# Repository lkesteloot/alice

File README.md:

# Alice website

Hardware projects from the 1990s and our revival and redesign starting in 2015 of that project and projects inspired by it. See the [web page](http://lkesteloot.github.io/alice/).

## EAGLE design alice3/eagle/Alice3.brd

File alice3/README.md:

# Alice III

This is the third model of the Alice machine. It runs a silicon Z80 with
two co-processors: an ARM for keyboard, disk, and serial port, and a Propeller for video.

The 80MHz Propeller has 48K of internal RAM, drives VGA and the 5-pin Aux connector (intended for audio but wired generically to 3 Propeller pins) and thus provides opportunities for video and other experimentation.

The 168MHz STM32F415 ARM Cortex-M4 contains 192K of RAM and is connected to a PS/2 port, an SD card, and a simple UART on a 2-pin header, and has a firmware monitor that can be altered or replaced.

In the `kicad` directory are various schematics and PCBs. The latest is
`MOBO_SMD`, which uses surface mount versions of the parts.

To bring up a new board:

* Power:
    * Use a wall wart to provide micro-USB power. Verify that the D2 LED
      (closest to the switches) is on.  If you have an in-line USB
      current meter, there should be less than 10 mA being initially pulled.
      (More is pulled later when the board is fully brought up.)
* Propeller:
    * Hook up the Prop Plug. The Vss pin should be closest to the corner of
      the board.
    * Run PropellerIDE, load the `video_board/propeller/Main.spin` file,
      and program the EEPROM. After this you should be able to hook up a VGA
      monitor and see the line `Alice 3 GPU firmware`.
    * Remove the Prop Plug.
* Cortex-M4:
    * Connect your computer to the USB jack of the Alice III.
    * Short the header closest to the ARM, labeled "JP1".
    * Hard-reset the board (the push button closest to the LEDs).
    * Wait one second, then remove the jumper.  If you look in your
      USB device list, you should see the STM bootloader.  For example,
      on MacOS X, the output of `system_profiler SPUSBDataType` should
      contain a section similar to:
```
        STM32  BOOTLOADER:

          Product ID: 0xdf11
          Vendor ID: 0x0483  (STMicroelectronics)
          Version: 22.00
          Serial Number: 366A34573335
          Speed: Up to 12 Mb/sec
          Manufacturer: STMicroelectronics
          Location ID: 0x14100000 / 20
          Current Available (mA): 1000
          Current Required (mA): 100
          Extra Operating Current (mA): 0
```
    * In `binaries`, run `sh install_cortex_m4_firmware.sh`.
        * `dfu-util` is a prerequisite.  It can be installed
	  on MacOS (our primary platform) through MacPorts, or you
	  can compile it from the source at
          `git://git.code.sf.net/p/dfu-util/dfu-util`.
    * To interact with the boot monitor:
        * Locate the 2-pin header closest to the MicroSD socket.
          There's no label on this header.
        * Attach a serial transceiver to this header; transmit to the pin
          closest to the ARM, and receive from the other pin.
          E.g. connect FTDI Tx to the pin closer to the ARM and
          FTDI Rx to the pin further from the ARM.
        * Connect to the serial port at 115200 baud.
        * When you hard-reset or power-on the Alice III, you should see
          on the serial port "Alice 3 I/O firmware" followed by the
          firmware build date.
* Z80:
    * Format a MicroSD card for FAT32.
    * Copy `binaries/bootrom.bin`, `binaries/boot.dsk` and `binaries/disks.txt` to the MicroSD card.
    * Install the MicroSD card in the Alice III and power-on or hard-reset the Alice III.

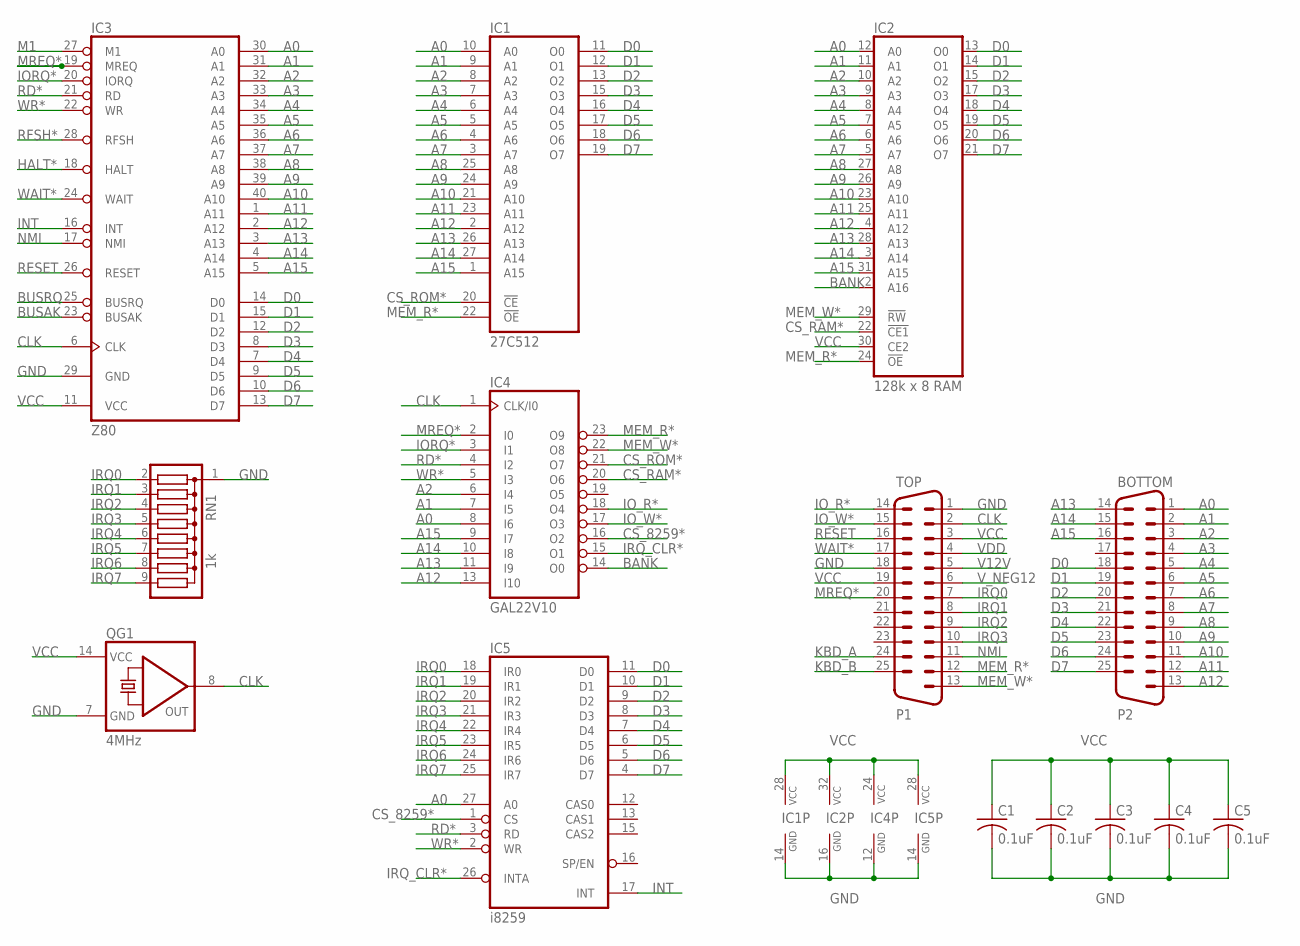
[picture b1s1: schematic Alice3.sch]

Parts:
BOTTOM: P2; M25HP
C1, C2, C3, C4, C5: 0.1uF; C1206
IC1: 27C512; DIL28
IC2: 128k x 8 RAM; DIL32
IC3: Z80; DIL40
IC4: GAL22V10; DIL24-3
IC5: i8259; DIL28-6
QG1: 4MHz; DIL14S
RN1: 1k; SIL9
TOP: P1; M25HP

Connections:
A0: BOTTOM.1, IC1.10 (A0), IC2.12 (A0), IC3.30 (A0), IC4.8 (I6), IC5.27 (A0)
A1: BOTTOM.2, IC1.9 (A1), IC2.11 (A1), IC3.31 (A1), IC4.7 (I5)
A2: BOTTOM.3, IC1.8 (A2), IC2.10 (A2), IC3.32 (A2), IC4.6 (I4)
A3: BOTTOM.4, IC1.7 (A3), IC2.9 (A3), IC3.33 (A3)
A4: BOTTOM.5, IC1.6 (A4), IC2.8 (A4), IC3.34 (A4)
A5: BOTTOM.6, IC1.5 (A5), IC2.7 (A5), IC3.35 (A5)
A6: BOTTOM.7, IC1.4 (A6), IC2.6 (A6), IC3.36 (A6)
A7: BOTTOM.8, IC1.3 (A7), IC2.5 (A7), IC3.37 (A7)
A8: BOTTOM.9, IC1.25 (A8), IC2.27 (A8), IC3.38 (A8)
A9: BOTTOM.10, IC1.24 (A9), IC2.26 (A9), IC3.39 (A9)
A10: BOTTOM.11, IC1.21 (A10), IC2.23 (A10), IC3.40 (A10)
A11: BOTTOM.12, IC1.23 (A11), IC2.25 (A11), IC3.1 (A11)
A12: BOTTOM.13, IC1.2 (A12), IC2.4 (A12), IC3.2 (A12), IC4.13 (I10)
A13: BOTTOM.14, IC1.26 (A13), IC2.28 (A13), IC3.3 (A13), IC4.11 (I9)
A14: BOTTOM.15, IC1.27 (A14), IC2.3 (A14), IC3.4 (A14), IC4.10 (I8)
A15: BOTTOM.16, IC1.1 (A15), IC2.31 (A15), IC3.5 (A15), IC4.9 (I7)
BANK: IC2.2 (A16), IC4.14 (O0)
BUSAK: IC3.23 (BUSAK)
BUSRQ: IC3.25 (BUSRQ)
CLK: IC3.6 (CLK), IC4.1 (CLK/I0), QG1.8 (OUT), TOP.2
CS_8259*: IC4.16 (O2), IC5.1 (CS)
CS_RAM*: IC2.22 (!CE1), IC4.20 (O6)
CS_ROM*: IC1.20 (!CE), IC4.21 (O7)
D0: BOTTOM.18, IC1.11 (O0), IC2.13 (O0), IC3.14 (D0), IC5.11 (D0)
D1: BOTTOM.19, IC1.12 (O1), IC2.14 (O1), IC3.15 (D1), IC5.10 (D1)
D2: BOTTOM.20, IC1.13 (O2), IC2.15 (O2), IC3.12 (D2), IC5.9 (D2)
D3: BOTTOM.21, IC1.15 (O3), IC2.17 (O3), IC3.8 (D3), IC5.8 (D3)
D4: BOTTOM.22, IC1.16 (O4), IC2.18 (O4), IC3.7 (D4), IC5.7 (D4)
D5: BOTTOM.23, IC1.17 (O5), IC2.19 (O5), IC3.9 (D5), IC5.6 (D5)
D6: BOTTOM.24, IC1.18 (O6), IC2.20 (O6), IC3.10 (D6), IC5.5 (D6)
D7: BOTTOM.25, IC1.19 (O7), IC2.21 (O7), IC3.13 (D7), IC5.4 (D7)
GND: C1.2, C2.2, C3.2, C4.2, C5.2, IC1.14 (GND), IC2.16 (GND), IC3.29 (GND), IC4.12 (GND), IC5.14 (GND), QG1.7 (GND), RN1.1, TOP.1, TOP.18
HALT*: IC3.18 (HALT)
INT: IC3.16 (INT), IC5.17 (INT)
IORQ*: IC3.20 (IORQ), IC4.3 (I1)
IO_R*: IC4.18 (O4), TOP.14
IO_W*: IC4.17 (O3), TOP.15
IRQ0: IC5.18 (IR0), RN1.2, TOP.7
IRQ1: IC5.19 (IR1), RN1.3, TOP.8
IRQ2: IC5.20 (IR2), RN1.4, TOP.9
IRQ3: IC5.21 (IR3), RN1.5, TOP.10
IRQ4: IC5.22 (IR4), RN1.6
IRQ5: IC5.23 (IR5), RN1.7
IRQ6: IC5.24 (IR6), RN1.8
IRQ7: IC5.25 (IR7), RN1.9
IRQ_CLR*: IC4.15 (O1), IC5.26 (INTA)
KBD_A: TOP.24
KBD_B: TOP.25
M1: IC3.27 (M1)
MEM_R*: IC1.22 (!OE), IC2.24 (!OE), IC4.23 (O9), TOP.12
MEM_W*: IC2.29 (!RW), IC4.22 (O8), TOP.13
MREQ*: IC3.19 (MREQ), IC4.2 (I0), TOP.20
NMI: IC3.17 (NMI), TOP.11
RD*: IC3.21 (RD), IC4.4 (I2), IC5.3 (RD)
RESET: IC3.26 (RESET), TOP.16
RFSH*: IC3.28 (RFSH)
V12V: TOP.5
VCC: C1.1, C2.1, C3.1, C4.1, C5.1, IC1.28 (VCC), IC2.30 (CE2), IC2.32 (VCC), IC3.11 (VCC), IC4.24 (VCC), IC5.28 (VCC), QG1.14 (VCC), TOP.3, TOP.19
VDD: TOP.4
V_NEG12: TOP.6
WAIT*: IC3.24 (WAIT), TOP.17
WR*: IC3.22 (WR), IC4.5 (I3), IC5.2 (WR)

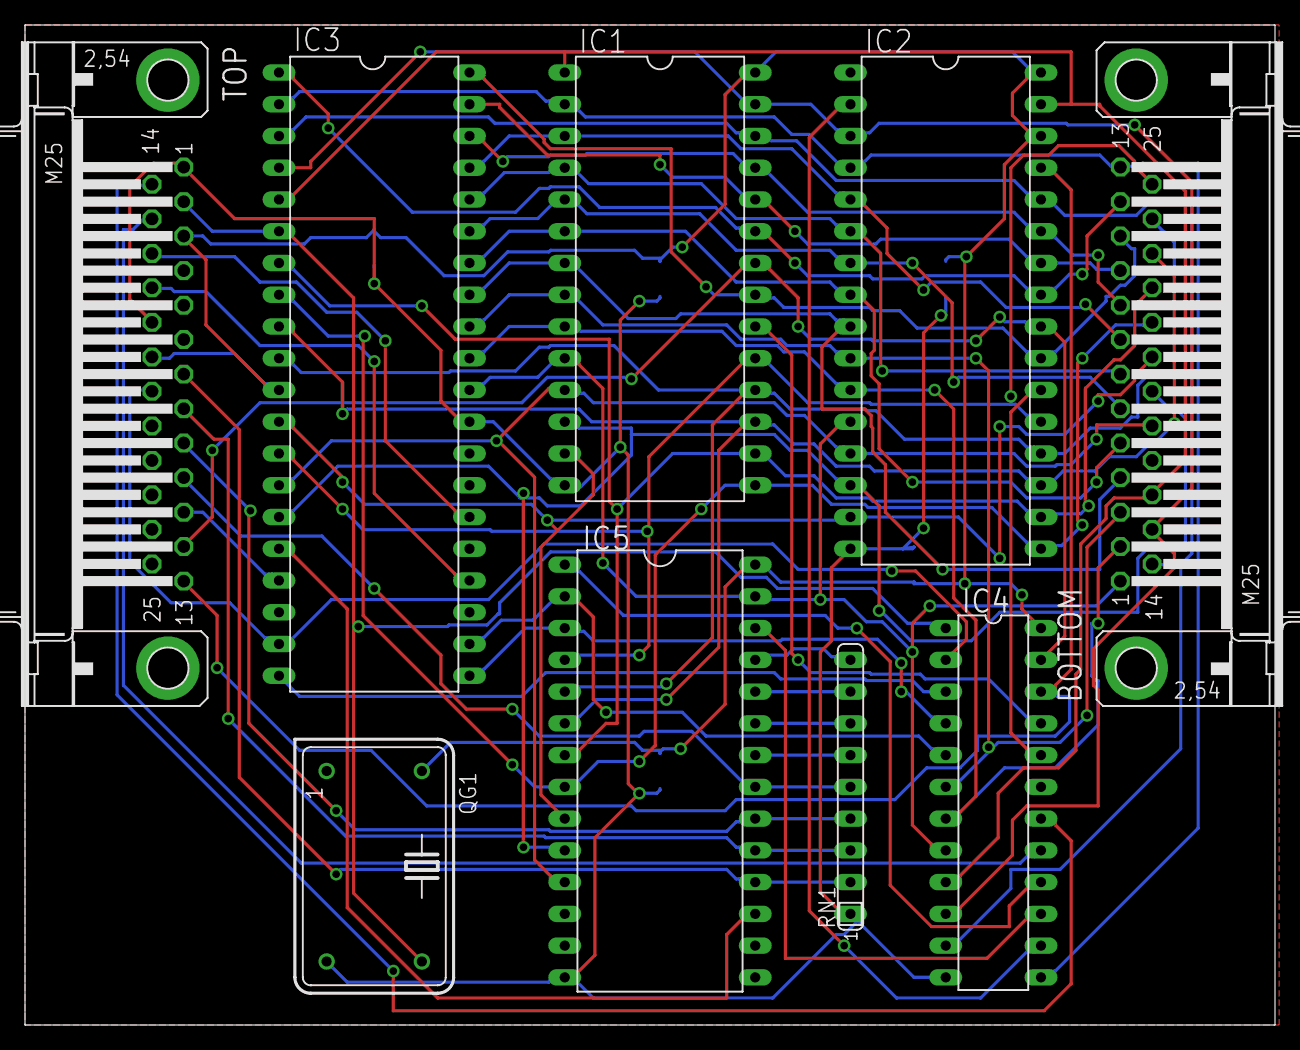
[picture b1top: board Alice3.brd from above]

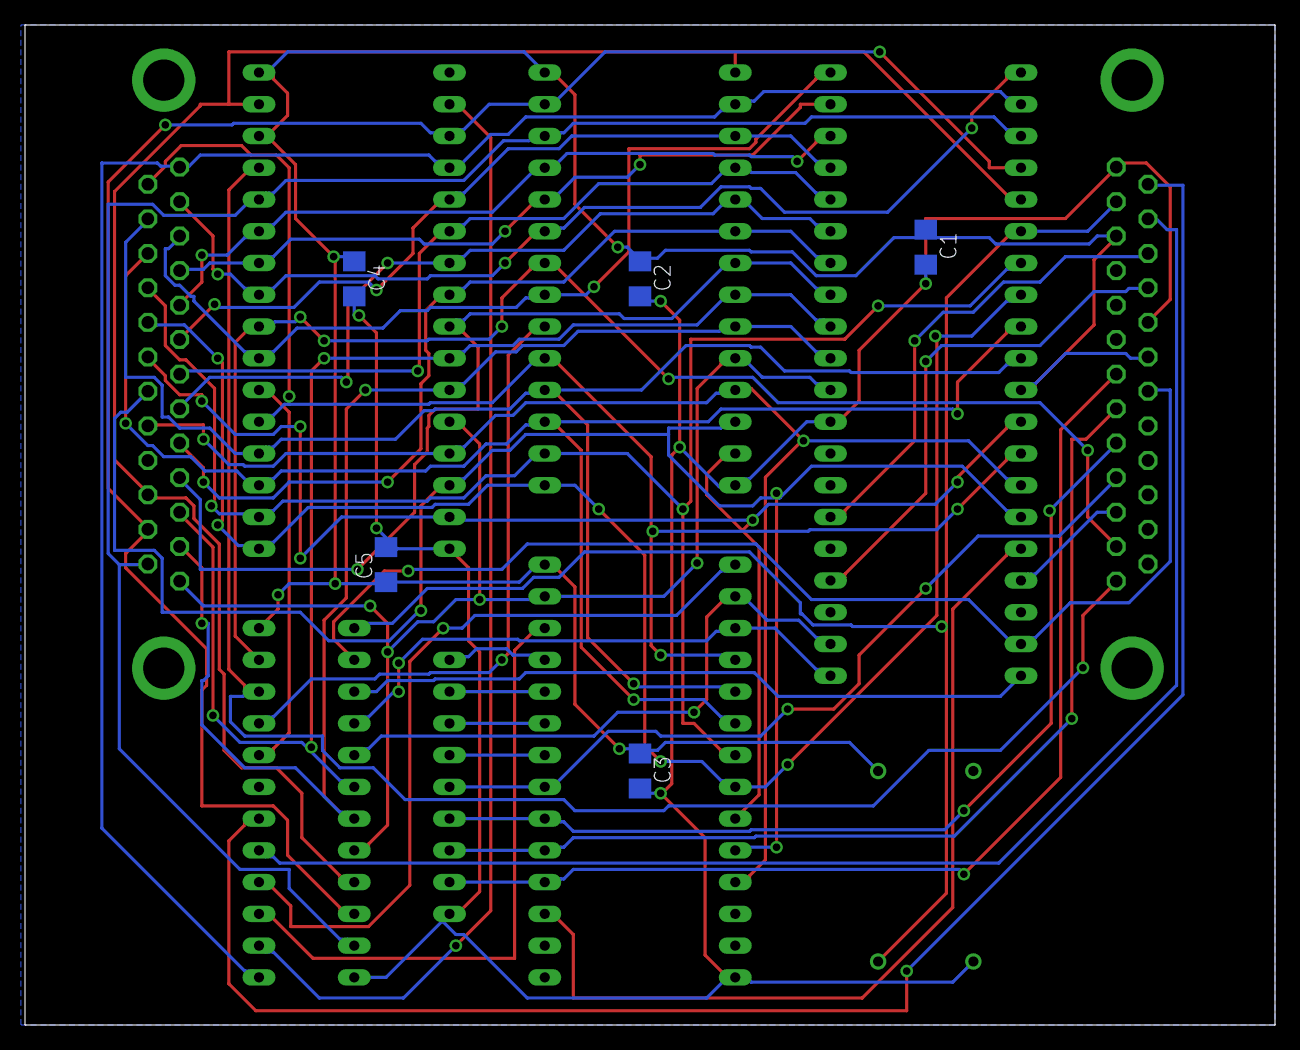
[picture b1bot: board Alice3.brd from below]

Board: 2 copper layers, 100.0 x 80.0 mm, 14 parts (5 on the bottom side), 52 nets.

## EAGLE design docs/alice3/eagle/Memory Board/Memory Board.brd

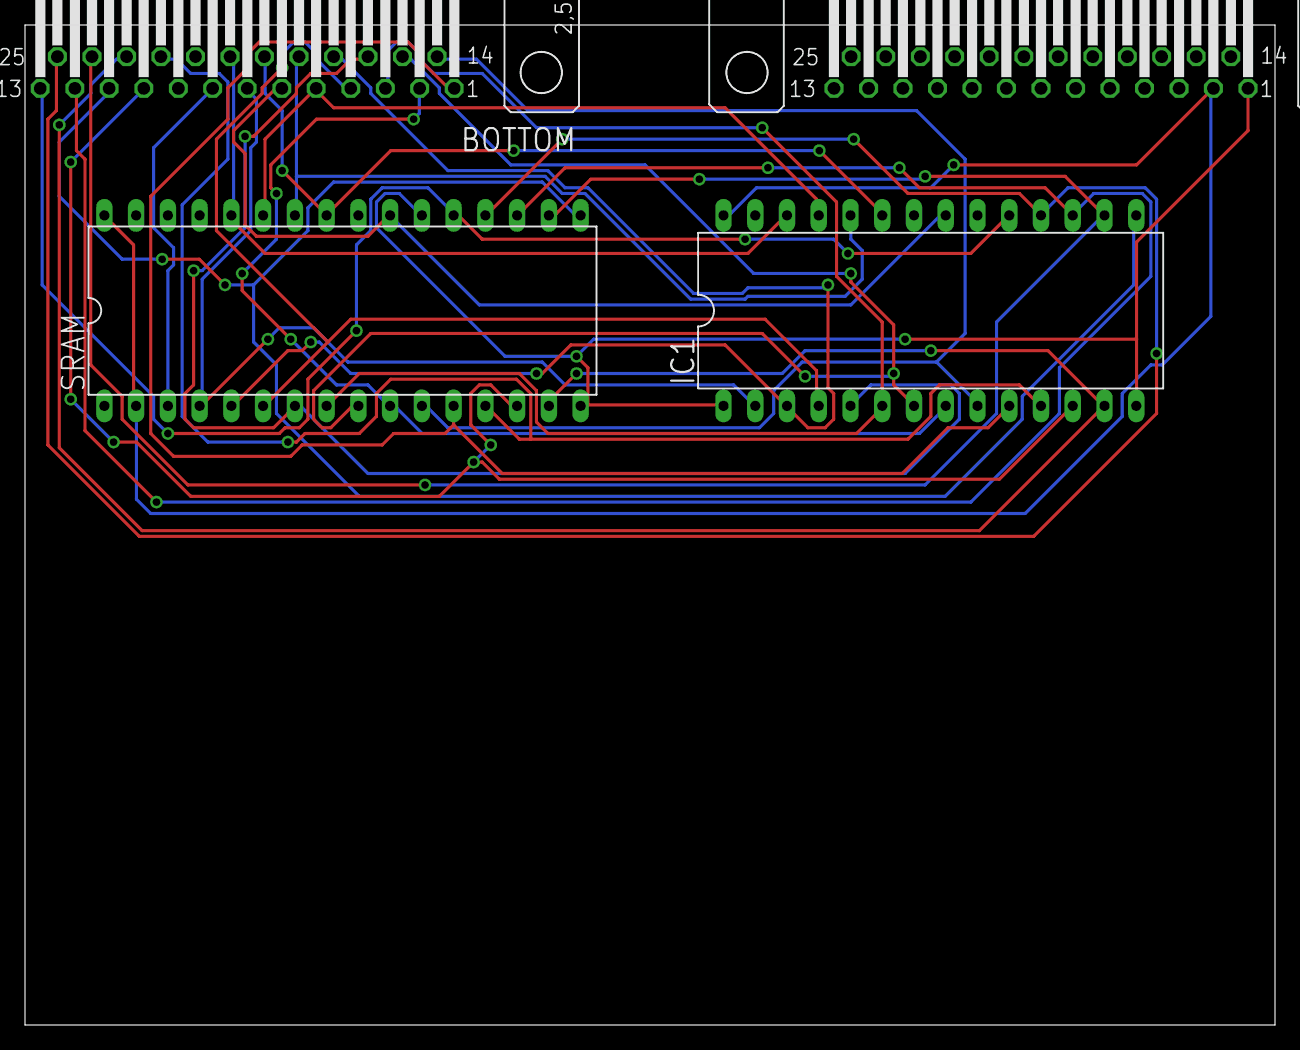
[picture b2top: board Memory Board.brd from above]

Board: 2 copper layers, 100.0 x 80.0 mm, 4 parts (0 on the bottom side), 25 nets.

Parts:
BOTTOM: M25H
IC1: 27C128P; DIL28-6
SRAM: DIL32
TOP: M25H

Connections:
+5: IC1.28, SRAM.2, SRAM.32, TOP.2
A0: BOTTOM.1, IC1.10, SRAM.12
A1: BOTTOM.14, IC1.9, SRAM.11
A2: BOTTOM.2, IC1.8, SRAM.10
A3: BOTTOM.15, IC1.7, SRAM.9
A4: BOTTOM.3, IC1.6, SRAM.8
A5: BOTTOM.16, IC1.5, SRAM.7
A6: BOTTOM.4, IC1.4, SRAM.6
A7: BOTTOM.17, IC1.3, SRAM.5
A8: BOTTOM.5, IC1.25, SRAM.27
A9: BOTTOM.18, IC1.24, SRAM.26
A10: BOTTOM.6, IC1.21, SRAM.23
A11: BOTTOM.19, IC1.23, SRAM.25
A12: BOTTOM.7, IC1.2, SRAM.4
A13: BOTTOM.20, IC1.26, SRAM.28
A14: BOTTOM.8, SRAM.3
D0: BOTTOM.22, IC1.11, SRAM.13
D1: BOTTOM.10, IC1.12, SRAM.14
D2: BOTTOM.23, IC1.13, SRAM.15
D3: BOTTOM.11, IC1.15, SRAM.17
D4: BOTTOM.24, IC1.16, SRAM.18
D5: BOTTOM.12, IC1.17, SRAM.19
D6: BOTTOM.25, IC1.18, SRAM.20
D7: BOTTOM.13, IC1.19, SRAM.21
GND: IC1.1, IC1.14, SRAM.16, SRAM.22, TOP.1

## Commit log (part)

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2017-04-15 Fix various bugs in FIFO code.
2017-04-15 Can increment in memtool.
2017-04-15 Convert image to 32bits before accessing
2017-04-16 Pretty stable frame buffer.
2017-04-16 Double size of FIFO to avoid underrun.
2017-04-16 Encapsulate touchscreen in its own unit
2017-04-16 Add beginnings of events on hardware
2017-04-16 Add ERROR prints on unexpected conditions
2017-04-17 Move flush so gl.c is not dependent on network
2017-04-17 Add platform.mk file for choosing implementation
    Edit platform.mk to change the implementaiton of the rasterizer and events.
2017-04-17 More careful LCD pixel output.
2017-04-19 Convert output to G's
2017-04-24 Add second memory interface.
2017-04-24 Modify memtool to support 64-bit writes and reads.
2017-04-24 Protocol test program.
2017-04-24 Draw bounding box of triangle.
2017-04-24 Turn of debug printf and usleep() now that we block on swap buffers.
2017-04-25 Respect triangle color; display count of unhandled commands.
2017-04-25 Make GPU command buffer - not tested
2017-04-26 Correct check for mmap() failure (not compiled or tested).
2017-04-26 Change DEBUG_PRINT to undef
2017-04-27 Reset buffer after each frame.
2017-04-27 Put image in both framebuffers
    Make new put_image function.
    Put the fipImage in both framebuffers that may be scanned out.
    Center image correctly in dimensions less than the framebuffer size.
2017-04-27 Add a utility to save the framebuffers as images
    Save off each framebuffer using FreeImagePlus.
    FIP will automatically use an encoder matching the filename extension entered.
    e.g. sudo alice4save framebuffer0.png framebuffer1.jpg # not that you'd do this, but it works
    Hardcode the framebuffer location, rowbytes, and bpp for convenience.
2017-04-28 Spin triangle more slowly in the test.
2017-04-28 Disable networking in Arena, it doesn't compile on the embedded Linux.
2017-04-29 Bigger FB FIFO and latch the debug text.
2017-04-30 Compare open against -1 to detect failure
    OMG, this is kind of embarrassing.
2017-04-30 Fix tied evaluator record and read
    Fix cut-and-paste error in tied evaluator loop - set loop variable k but did not use it to read evaluator device
    Fix events_tie() - was not using the correct array index
2017-05-01 Software side of pattern.
2017-05-01 Add code to parse PATTERN (untested)
2017-05-01 Implement patterns in FPGA.
2017-05-02 Add pattern test to protocol program.
2017-05-02 Add optimization to all Makefiles
    This change boosts logo's CPU-only frame rate from 25 frames per second to 95.
2017-05-03 Double-buffer the command stream
    If "double_buffer_commands" is set to 0, commands are written directly to the GPU memory buffer for commands. (Therefore no additional commands can be safely written to the buffer until the GPU has f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
    If "double_buffer_commands" is set to 1, commands are written directly to a separate "staging" memory buffer. "swap" waits until any previous GPU work is complete, meaning the GPU buffer can be writt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
    N.B. By default now set double_buffer_commands to 1. It is a const variable me
2017-05-03 Expose front buffer bit.
2017-05-04 Add frame stats per-frame and averaged over a second
    PRINT_FRAME_STATS=1 will print ms for some portions of the frame every second.
    PRINT_FRAME_STATS=2 will print ms for some portions of the frame every frame.
2017-05-04 Program to pulse LCD backlight.
2017-05-04 Fix bounding box calculation.
2017-05-04 Modify fpgasim to do more efficient color interpolation.
2017-05-04 Print time spent waiting on raster finish
2017-05-04 Revert accidental change to platform makefile.
2017-05-04 Write overlay in single-bit red so as to not disturb the LCD. Need to investigate why this is necessary.
2017-05-05 add -lm for Linux build
2017-05-08 Tilt test over VNC
    Prints "TILT_VALID" and tilt valuators when tilt is within accurate ranges.
    Prints "TILT_INVALID" and does not print valuators when tilt is out of range.
2017-05-13 Add two stages to the reciprocal (from 4 to 6) to eliminate timing warnings.
    Fixes #34.
2017-05-17 Add modes for just ramp and for delaying all bits
    Change size to 800x480 so that output matches Alice 4 display
    - notably the ramp can be loaded into Alice 4 display to illustrate issues
    "make" creates all three images.
    Provide "--all8bits" to delay all 8 bits of the color, showing close to what Brad sees.
    Provide "--justramp" to output the color ramp with no output effect.
2017-05-18 Add Z buffer test to protocol.cpp.
2017-05-22 DISPLAY_ENABLE -> DATA_ENABLE
2017-05-22 Add some boards and chips we're using
    Adafruit Bluefruit LE SPI
    Adafruit L3GD20H breakout
    Adafruit PowerBoost 1000c
    STM STMPE811
2017-05-22 Add memory controller ports for Z.
2017-05-24 Add write FIFO and use it for color.
2017-05-24 Interpolate Z.
2017-05-24 Move i2c functions into utility module
2017-05-24 Accelerometer module
2017-05-24 Fix math error converting radians to degres
2017-05-24 Smooth accelerometer with exponential decay
    Add (current sensor reading * (1 - decay)) to (old * decay).
    Smoothing helps somewhat with decay = .5. Decay = .8 looks a lot better but loses rapid motion.
    Committing decay = 0.5.
2017-05-25 Clean up Verilog code.
2017-05-26 Fix Z buffer artifacts. Fixes #13.
2017-05-26 Add stats to protocol test.
2017-05-26 Clear Z in protocol test.
2017-05-28 Remove test code.
2017-05-28 Add notes for test fifo.
2017-05-29 Speed up rasterization. Fixes #40.
2017-05-29 Fix use of fifo.empty in read fifo.
2017-06-02 Always spin object slowly, fix Z
    Remove call to gversion and machine-dependent Z setup.
    Use default Z function, back-to-front values for lsetdepth, and clear Z to far.
    Set "spin" to default to TRUE and spin 1/3 as fast as it was spinning.
2017-06-03 Add tilt
2017-06-04 Rasterize lines
2017-06-04 Rasterize lines more correctly
    Draw boxes that represent lines by extending line by linewidth along
    axis perpendicular to the line's major axis, resulting in parallelograms.
2017-06-04 Factor out libawesome.
2017-06-04 Add home support to protocol test program.
2017-06-04 Use one global Awesome
    Move struct definition into awesome.c.
    Keep one global Awesome instance in awesome.c.
    Remove all Awesome pointers from awesome functions.
    Fixup protocol test to match.
2017-06-04 Don't pass a pointer to an Awesome
2017-06-04 Warn if we skip a frame.
2017-06-04 Add Arena
2017-06-04 compile with networking
2017-06-04 Implement czclear(), fix #39
    Implement czclear in rasterizer interface and rasterizer implementations.
    In hardware_rasterizer, pass czclear to libawesome
    Use czclear in logo and jello (already used in bounce)
2017-06-04 Set ESC (Home) to exit only submenus in buttonfly
2017-06-04 Add ability to dump logo commands to a file. For #22.
2017-06-04 Add Make target for writing logo.bin to SD card.
2017-06-05 Add memory thrashing tool.
2017-06-11 Fix line endings for u-boot.txt.
2017-06-12 Re-enable double buffering of commands.
2017-06-12 Break up long thin triangles. For issue #17.
    Long thin (diagonal) triangles waste a lot of time in the
    rasterizer because we consider every point in the bounding
    box. With this change, if the ratio of triangle pixels
    to bounding box pixels is low, we tesselate the triangle.
    This halves the number of bounding box pixels (1.8m to 0.9m)
    at the slowest frame of buttonfly. (The bevel of the button
2017-06-12 Configure extra memory ports.
2017-06-16 add network events example in a comment
2017-06-16 fix array overrun
2017-06-16 Avoid divide by zero when displaying statistics.
2017-06-16 Don't start reading command buffer until we're ready.
2017-06-16 Bogus no-op changes by Quartus.
2017-07-15 Update overview page.
2017-07-15 Fix up Alice 2 docs.
2017-07-15 Load fonts over https.
2017-07-15 Use arabic numerals instead of roman ones for Alice version numbers.
2017-07-15 Add stub Alice 4 page.
2017-07-20 Disable blinking LED.
2017-07-26 Don't show arena instructions. Fixes #58.
2017-07-26 Add disabled code to split up lines.
2017-08-02 Add Makefile targets to start/stop service.
2017-08-03 IrisGL transformation and lighting benchmark
2017-08-04 Don't enable shutdown in Makefile.
2017-08-04 Dummy events in platform Makefile.
2017-08-05 Fix aspect ratio of ideas.
2017-08-05 Replace shutdown with ideas.
2017-08-06 Final flight changes to make it build.
2017-08-06 Fix flight warnings and clear bug in gl.
2017-08-08 Run the 747 by default in flight.
2017-08-09 Link to web page.
2017-08-09 Add secret menu.
2017-08-10 switch interaction to that of jello
2017-08-10 render all 6 walls with faceculling
2017-08-15 Big VCF West 2017 commit
    Terminal.spin: complete rewrite in prop asm, lots more codes handled,
    jump table used which should provide a good example for streamlining in
    the future
    Bus_interface.spin: better documentation at the top, added serial terminal
    mirroring but commented-out, added ay_allatonce handler, added ay_BEL
    Main.spin: added another row to the buffer for easier terminal scrolling
2017-08-15 Added JDCogSerial.spin to alice3/video_board/propeller directory since the alternative commented-out terminal code in Main.spin references it
2017-08-16 make CE2 high
2017-08-16 draft DABO2 PCB
2017-08-16 footprints
2017-08-17 increase SD speed to about 21MHz after init
2017-08-17 ARM fimware binary with faster SD access
2017-08-19 catch correct enum for WRITE_DMA
2017-08-19 implement ARM firmware for DMA READ and WRITE
2017-08-26 set up RFSH and WAIT signals correctly
2017-08-28 1st set MOBO schematic fixes for 1st PCBWay spin
    Various fixes for KiCAD messing up components
    Button on BOOT0
    No huge cap on power supply LED
    Discard RAM
    Route ARM to Z80 /WAIT and /RFSH
    Use "~" for active-low lines (shown in schematic by line above them)
2017-08-29 V4 improvements round 2
    Label buttons, LEDs, and connectors
    Delete footprints for deleted schematic parts
    Move microUSB jack and space out PS2, VGA connectors
    Position SMT Propeller crystal
    Change BOOT0 header to button
    Delete RAM
2017-08-29 consolidate all Z80 addr pins on one ARM port
2017-09-06 fix misspelling of "staging"
2017-09-07 constant current part FAN5333A/B
2017-09-07 integrate constant current driver, drop TFT Friend
2017-09-08 replace L3DG20H breakout with actual chip
2017-09-09 TPS61090 boost supply
2017-09-10 add source files for components
2017-09-11 run LIPO to STMPE811 ADC on IN0
2017-09-13 Add link to red button.
2017-09-13 Acrylic enclosure.
2017-09-13 l3gd20h qfn footprint
2017-09-13 first draft of layout
2017-09-14 add hidden PAD pins that are GND
2017-09-14 Second draft of layout
    Lawrence fixes to schematic
    Layout PCB
2017-09-16 remove R pulling PWREN to VBAT
2017-09-17 one more draft layout; better 3v3 plane
2017-09-18 add SMD 1206 testpoint pad footprint
2017-09-18 Hopefully near final layout
2017-09-27 Add jac library including large hole
2017-09-29 add ideas
2017-09-29 rotate 180 degrees
2017-10-10 Fix up WaveDrom for write FIFO.
2017-10-12 Minor tweaks to write-up.
2017-10-16 Better motivation for area reciprocal.
2017-10-16 Get flight to compile on Alice 4.
2017-10-16 Slower accelerator decay.
2017-10-16 Fix secret menu.
2017-10-16 Re-enable culling, implement correctly
    Ideas now works and the bounce models (except for doughnut?!) work properly and at full rate
2017-10-22 Start Verilator simulation integration.
2017-10-22 Add Frame buffer to Verilator.
2017-10-24 Add and link placeholder for libgl page
2017-10-25 Add more about libgl and the platform files
2017-10-25 Fix FPG to FPGA
2017-11-09 Undo accidental change to secret menu in buttonfly.
2017-11-09 Can exit flight with Esc key.
2017-11-09 Better accelerometer for jello.
2017-11-09 Add gyro library.
2017-11-09 Use accelerometer to move insect.
2017-11-19 Added tools page.
2017-11-19 In-progress sim work.
2017-11-27 Fix apostrophes.
2017-12-03 Add Grant Searle's BASIC + Alice 3 changes
2017-12-03 add Makefile
2017-12-06 Add tool to convert zasm .lst to az80 .prn for simualtor symbols
2018-01-04 Fix incorrectly rendered models in bounce
    I previously added backface in global initialization past to prevent
    the frontmost faces of the box from being rendered. Some of the
    models don't render properly with backface(TRUE). So enable backface
    only for the box.
2018-02-08 Remove remaining continue in libgl
    https://www.teamten.com/lawrence/programming/avoid-continue.html
2018-02-27 Sim: Don't modify internal signals, only modify top parameters.
2018-02-27 Sim: Go back to full-screen buffer.
2018-02-27 Sim: Simulate command buffer.
2018-02-28 Sim: Draw test triangle.
2018-03-03 Add NOTES file about binary command stream file.
2018-04-27 Minor tweaks to docs.
2018-05-06 Fix up XXX comments.
2018-05-24 Clarify members page.
2018-05-24 Yet more members formatting.
2018-06-06 Remove VNC library
2018-10-13 NASCOM BASIC does not support "ELSE" clauses on "IF" statements. Some lines were still too long. Fixed some semantic errors introduced by breaking long lines earlier.
2019-03-16 Embed YouTube videos of Alice 4 presentation.

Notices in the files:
parts and their libraries:
SparkFun-Connectors: Licensing: Creative Commons ShareAlike 4.0 International - https://creativecommons.org/licenses/by-sa/4.0
